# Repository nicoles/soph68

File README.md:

# soph68

Hey look, another 65%! 
This one has no underglow or hotswap, uses the magicforce layout. Very compatible layout for keycap sets, takes pcb mount stabs, supports single color led backlight.

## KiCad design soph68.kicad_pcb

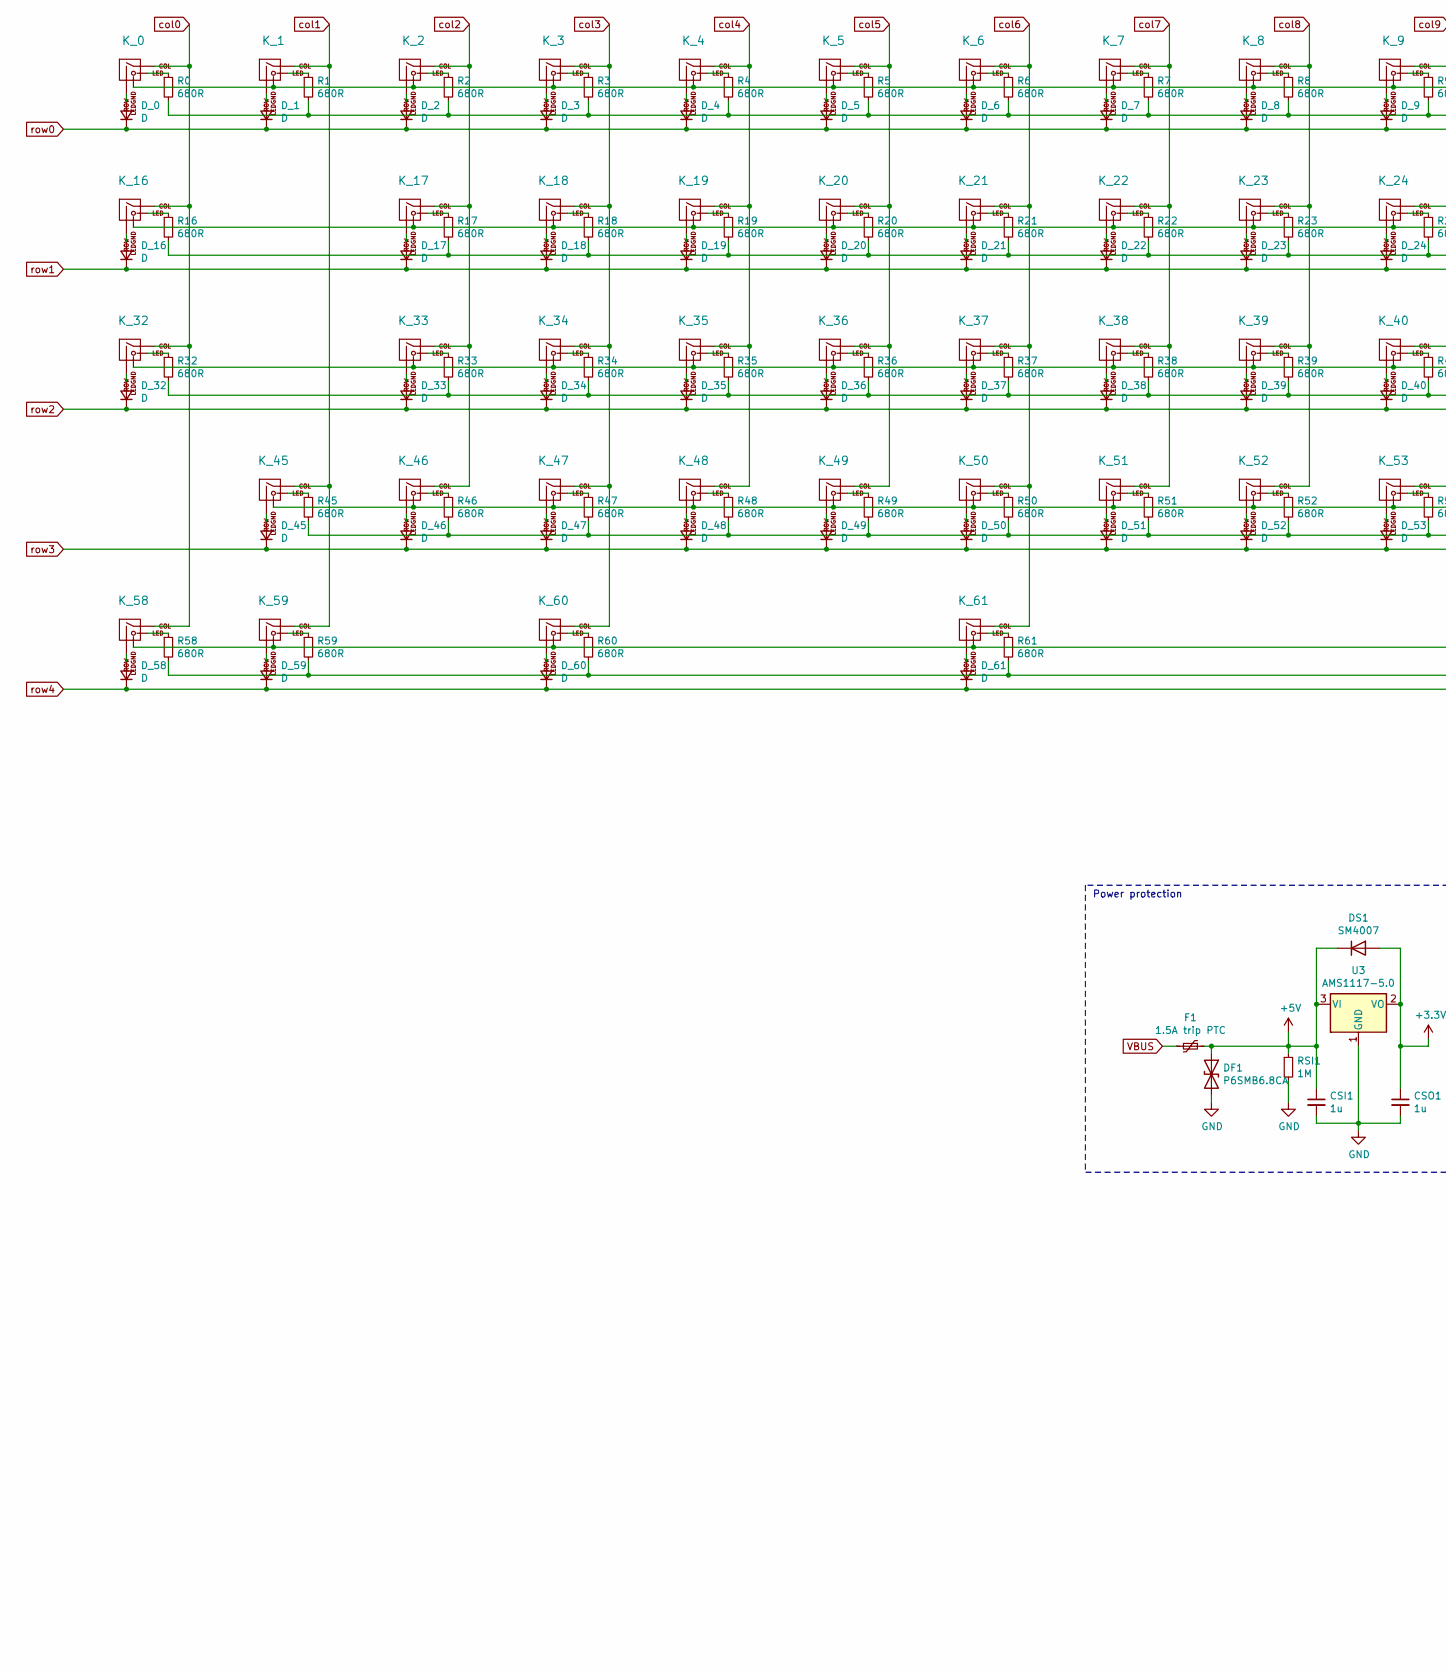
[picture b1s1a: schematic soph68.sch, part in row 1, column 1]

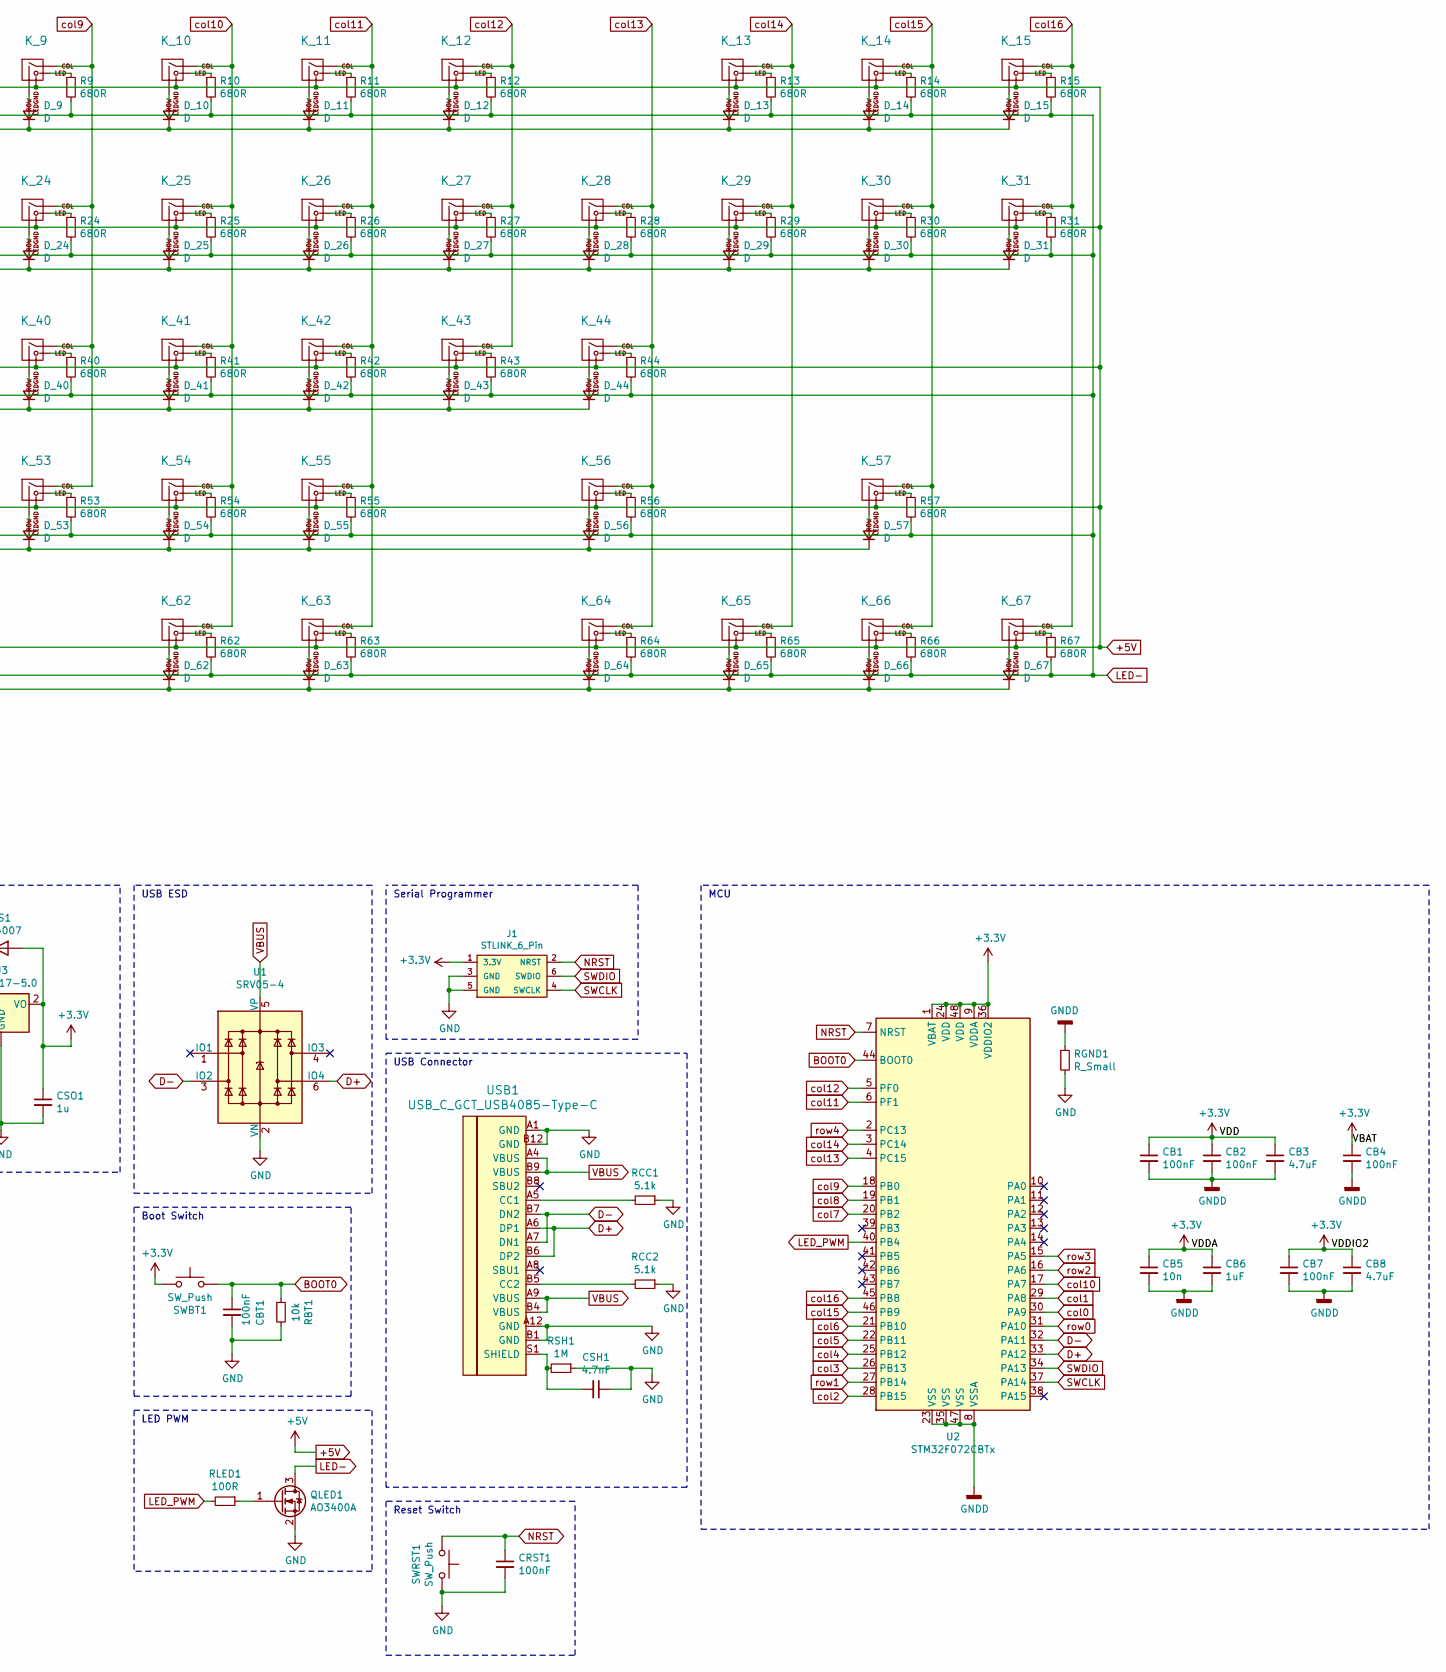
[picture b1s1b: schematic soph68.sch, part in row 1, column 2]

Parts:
CB1, CB2, CB4, CB7: 100nF; C_0402_1005Metric; JLCCode C1525
CB3, CB8: 4.7uF; C_0402_1005Metric; JLCCode C23733
CB5: 10n; C_0402_1005Metric; JLCCode C15195
CB6: 1uF; C_0402_1005Metric; JLCCode C52923
CBT1: 100nF; C_0402_1005Metric; JLCCode C1525
CRST1: 100nF; C_0402_1005Metric; JLCCode C1525
CSH1: 4.7nF; C_0805_2012Metric; JLCCode C1744
CSI1: 1u; C_0805_2012Metric; JLCCode C28323
CSO1: 1u; C_0805_2012Metric; JLCCode C28323
DF1: P6SMB6.8CA; D_SMB; JLCCode C78395
DS1: SM4007; D_MELF; JLCCode C64898
D_0, D_1, D_2, D_3, D_4, D_5, D_6, D_7, D_8, D_9, D_10, D_11, D_12, D_13, D_14, D_15, D_16, D_17, D_18, D_19, D_20, D_21, D_22, D_23, D_24, D_25, D_26, D_27, D_28, D_29, D_30, D_31, D_32, D_33, D_34, D_35, D_36, D_37, D_38, D_39, D_40, D_41, D_42, D_43, D_44, D_45, D_46, D_47, D_48, D_49, D_50, D_51, D_52, D_53, D_54, D_55, D_56, D_57, D_58, D_59, D_60, D_61, D_62, D_63, D_64, D_65, D_66, D_67: D; D_SOD-323F; JLCCode C81598
F1: 1.5A trip PTC; Fuse_1812_4532Metric; JLCCode C84140
J1: STLINK_6_Pin; 2X3_LOCK
K_0, K_1, K_2, K_3, K_4, K_5, K_6, K_7, K_8, K_9, K_10, K_11, K_12, K_14, K_15, K_17, K_18, K_19, K_20, K_21, K_22, K_23, K_24, K_25, K_26, K_27, K_28, K_30, K_31, K_33, K_34, K_35, K_36, K_37, K_38, K_39, K_40, K_41, K_42, K_43, K_46, K_47, K_48, K_49, K_50, K_51, K_52, K_53, K_54, K_55, K_57, K_65, K_66, K_67: KEYSW; MXOnly-1U
K_13: KEYSW; MXOnly-2U
K_16, K_29: KEYSW; MXOnly-1.5U
K_32: KEYSW; MXOnly-1.75U
K_44, K_45: KEYSW; MXOnly-2.25U
K_56: KEYSW; MXOnly-2.75U
K_58, K_59, K_60, K_62, K_63, K_64: KEYSW; MXOnly-1.25U
K_61: KEYSW; MXOnly-6.25U
QLED1: AO3400A; SOT-23; JLCCode C20917
R0, R1, R2, R3, R4, R5, R6, R7, R8, R9, R10, R11, R12, R13, R14, R15, R16, R17, R18, R19, R20, R21, R22, R23, R24, R25, R26, R27, R28, R29, R30, R31, R32, R33, R34, R35, R36, R37, R38, R39, R40, R41, R42, R43, R44, R45, R46, R47, R48, R49, R50, R51, R52, R53, R54, R55, R56, R57, R58, R59, R60, R61, R62, R63, R64, R65, R66, R67: 680R; R_0603_1608Metric; JLCCode C23228
RBT1: 10k; R_0805_2012Metric; JLCCode C17414
RCC1, RCC2: 5.1k; R_0805_2012Metric; JLCCode C27834
RGND1: R_Small; R_1206_3216Metric; JLCCode C127703
RLED1: 100R; R_0402_1005Metric; JLCCode C25076
RSH1: 1M; R_0805_2012Metric; JLCCode C17514
RSI1: 1M; C_0805_2012Metric; JLCCode C17514
SWBT1: SW_Push; SW_SPST_SKQG_WithStem; JLCCode C318884
SWRST1: SW_Push; SW_SPST_SKQG_WithStem; JLCCode C318884
U1: SRV05-4; SOT-23-6; JLCCode C85364
U2: STM32F072CBTx; LQFP-48_7x7mm_P0.5mm; JLCCode C81720
U3: AMS1117-5.0; SOT-223-3_TabPin2; JLCCode C6187
USB1: USB_C_GCT_USB4085-Type-C; USB_C_Receptacle_GCT_USB4085

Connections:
+3V3: CB1.1, CB2.1, CB3.1, CB4.1, CB5.1, CB6.1, CB7.1, CB8.1, CSO1.1, DS1.2 (A), J1.1 (3.3V), SWBT1.1, U2.1 (VBAT), U2.9 (VDDA), U2.24 (VDD), U2.36 (VDDIO2), U2.48 (VDD), U3.2 (VO)
+5V: CSI1.1, DF1.1 (A1), DS1.1 (K), F1.1, K_0.4 (LEDGND), K_1.4 (LEDGND), K_2.4 (LEDGND), K_3.4 (LEDGND), K_4.4 (LEDGND), K_5.4 (LEDGND), K_6.4 (LEDGND), K_7.4 (LEDGND), K_8.4 (LEDGND), K_9.4 (LEDGND), K_10.4 (LEDGND), K_11.4 (LEDGND), K_12.4 (LEDGND), K_13.4 (LEDGND), K_14.4 (LEDGND), K_15.4 (LEDGND), K_16.4 (LEDGND), K_17.4 (LEDGND), K_18.4 (LEDGND), K_19.4 (LEDGND), K_20.4 (LEDGND), K_21.4 (LEDGND), K_22.4 (LEDGND), K_23.4 (LEDGND), K_24.4 (LEDGND), K_25.4 (LEDGND), K_26.4 (LEDGND), K_27.4 (LEDGND), K_28.4 (LEDGND), K_29.4 (LEDGND), K_30.4 (LEDGND), K_31.4 (LEDGND), K_32.4 (LEDGND), K_33.4 (LEDGND), K_34.4 (LEDGND), K_35.4 (LEDGND), K_36.4 (LEDGND), K_37.4 (LEDGND), K_38.4 (LEDGND), K_39.4 (LEDGND), K_40.4 (LEDGND), K_41.4 (LEDGND), K_42.4 (LEDGND), K_43.4 (LEDGND), K_44.4 (LEDGND), K_45.4 (LEDGND), K_46.4 (LEDGND), K_47.4 (LEDGND), K_48.4 (LEDGND), K_49.4 (LEDGND), K_50.4 (LEDGND), K_51.4 (LEDGND), K_52.4 (LEDGND), K_53.4 (LEDGND), K_54.4 (LEDGND), K_55.4 (LEDGND), K_56.4 (LEDGND), K_57.4 (LEDGND), K_58.4 (LEDGND), K_59.4 (LEDGND), K_60.4 (LEDGND), K_61.4 (LEDGND), K_62.4 (LEDGND), K_63.4 (LEDGND), K_64.4 (LEDGND), K_65.4 (LEDGND), K_66.4 (LEDGND), K_67.4 (LEDGND), RSI1.1, U3.3 (VI)
BOOT0: CBT1.1, RBT1.1, SWBT1.2, U2.44 (BOOT0)
D+: U1.6 (IO4), U2.33 (PA12), USB1.A6 (DP1), USB1.B6 (DP2)
D-: U1.3 (IO2), U2.32 (PA11), USB1.A7 (DN1), USB1.B7 (DN2)
GND: CBT1.2, CRST1.2, CSH1.1, CSI1.2, CSO1.2, DF1.2 (A2), J1.3 (GND), J1.5 (GND), QLED1.2 (S), RBT1.2, RCC1.1, RCC2.1, RGND1.2, RSH1.1, RSI1.2, SWRST1.2, U1.2 (VN), U3.1 (GND), USB1.A1 (GND), USB1.A12 (GND), USB1.B1 (GND), USB1.B12 (GND)
GNDD: CB1.2, CB2.2, CB3.2, CB4.2, CB5.2, CB6.2, CB7.2, CB8.2, RGND1.1, U2.8 (VSSA), U2.23 (VSS), U2.35 (VSS), U2.47 (VSS)
LED-: QLED1.3 (D), R0.2, R1.2, R2.2, R3.2, R4.2, R5.2, R6.2, R7.2, R8.2, R9.2, R10.2, R11.2, R12.2, R13.2, R14.2, R15.2, R16.2, R17.2, R18.2, R19.2, R20.2, R21.2, R22.2, R23.2, R24.2, R25.2, R26.2, R27.2, R28.2, R29.2, R30.2, R31.2, R32.2, R33.2, R34.2, R35.2, R36.2, R37.2, R38.2, R39.2, R40.2, R41.2, R42.2, R43.2, R44.2, R45.2, R46.2, R47.2, R48.2, R49.2, R50.2, R51.2, R52.2, R53.2, R54.2, R55.2, R56.2, R57.2, R58.2, R59.2, R60.2, R61.2, R62.2, R63.2, R64.2, R65.2, R66.2, R67.2
LED_PWM: RLED1.2, U2.40 (PB4)
NRST: CRST1.1, J1.2 (NRST), SWRST1.1, U2.7 (NRST)
unnamed: CSH1.2, RSH1.2, USB1.S1 (SHIELD)
unnamed: D_0.2 (A), K_0.2 (ROW)
unnamed: D_1.2 (A), K_1.2 (ROW)
unnamed: D_2.2 (A), K_2.2 (ROW)
unnamed: D_3.2 (A), K_3.2 (ROW)
unnamed: D_4.2 (A), K_4.2 (ROW)
unnamed: D_5.2 (A), K_5.2 (ROW)
unnamed: D_6.2 (A), K_6.2 (ROW)
unnamed: D_7.2 (A), K_7.2 (ROW)
unnamed: D_8.2 (A), K_8.2 (ROW)
unnamed: D_9.2 (A), K_9.2 (ROW)
unnamed: D_10.2 (A), K_10.2 (ROW)
unnamed: D_11.2 (A), K_11.2 (ROW)
unnamed: D_12.2 (A), K_12.2 (ROW)
unnamed: D_13.2 (A), K_13.2 (ROW)
unnamed: D_14.2 (A), K_14.2 (ROW)
unnamed: D_15.2 (A), K_15.2 (ROW)
unnamed: D_16.2 (A), K_16.2 (ROW)
unnamed: D_17.2 (A), K_17.2 (ROW)
unnamed: D_18.2 (A), K_18.2 (ROW)
unnamed: D_19.2 (A), K_19.2 (ROW)
unnamed: D_20.2 (A), K_20.2 (ROW)
unnamed: D_21.2 (A), K_21.2 (ROW)
unnamed: D_22.2 (A), K_22.2 (ROW)
unnamed: D_23.2 (A), K_23.2 (ROW)
unnamed: D_24.2 (A), K_24.2 (ROW)
unnamed: D_25.2 (A), K_25.2 (ROW)
unnamed: D_26.2 (A), K_26.2 (ROW)
unnamed: D_27.2 (A), K_27.2 (ROW)
unnamed: D_28.2 (A), K_28.2 (ROW)
unnamed: D_29.2 (A), K_29.2 (ROW)
unnamed: D_30.2 (A), K_30.2 (ROW)
unnamed: D_31.2 (A), K_31.2 (ROW)
unnamed: D_32.2 (A), K_32.2 (ROW)
unnamed: D_33.2 (A), K_33.2 (ROW)
unnamed: D_34.2 (A), K_34.2 (ROW)
unnamed: D_35.2 (A), K_35.2 (ROW)
unnamed: D_36.2 (A), K_36.2 (ROW)
unnamed: D_37.2 (A), K_37.2 (ROW)
unnamed: D_38.2 (A), K_38.2 (ROW)
unnamed: D_39.2 (A), K_39.2 (ROW)
unnamed: D_40.2 (A), K_40.2 (ROW)
unnamed: D_41.2 (A), K_41.2 (ROW)
unnamed: D_42.2 (A), K_42.2 (ROW)
unnamed: D_43.2 (A), K_43.2 (ROW)
unnamed: D_44.2 (A), K_44.2 (ROW)
unnamed: D_45.2 (A), K_45.2 (ROW)
unnamed: D_46.2 (A), K_46.2 (ROW)
unnamed: D_47.2 (A), K_47.2 (ROW)
unnamed: D_48.2 (A), K_48.2 (ROW)
unnamed: D_49.2 (A), K_49.2 (ROW)
unnamed: D_50.2 (A), K_50.2 (ROW)
unnamed: D_51.2 (A), K_51.2 (ROW)
unnamed: D_52.2 (A), K_52.2 (ROW)
unnamed: D_53.2 (A), K_53.2 (ROW)
unnamed: D_54.2 (A), K_54.2 (ROW)
unnamed: D_55.2 (A), K_55.2 (ROW)
unnamed: D_56.2 (A), K_56.2 (ROW)
unnamed: D_57.2 (A), K_57.2 (ROW)
unnamed: D_58.2 (A), K_58.2 (ROW)
unnamed: D_59.2 (A), K_59.2 (ROW)
unnamed: D_60.2 (A), K_60.2 (ROW)
unnamed: D_61.2 (A), K_61.2 (ROW)
unnamed: D_62.2 (A), K_62.2 (ROW)
unnamed: D_63.2 (A), K_63.2 (ROW)
unnamed: D_64.2 (A), K_64.2 (ROW)
unnamed: D_65.2 (A), K_65.2 (ROW)
unnamed: D_66.2 (A), K_66.2 (ROW)
unnamed: D_67.2 (A), K_67.2 (ROW)
unnamed: K_0.3 (LED), R0.1
unnamed: K_1.3 (LED), R1.1
unnamed: K_2.3 (LED), R2.1
unnamed: K_3.3 (LED), R3.1
unnamed: K_4.3 (LED), R4.1
unnamed: K_5.3 (LED), R5.1
unnamed: K_6.3 (LED), R6.1
unnamed: K_7.3 (LED), R7.1
unnamed: K_8.3 (LED), R8.1
unnamed: K_9.3 (LED), R9.1
unnamed: K_10.3 (LED), R10.1
unnamed: K_11.3 (LED), R11.1
unnamed: K_12.3 (LED), R12.1
unnamed: K_13.3 (LED), R13.1
unnamed: K_14.3 (LED), R14.1
unnamed: K_15.3 (LED), R15.1
unnamed: K_16.3 (LED), R16.1
unnamed: K_17.3 (LED), R17.1
unnamed: K_18.3 (LED), R18.1
unnamed: K_19.3 (LED), R19.1
unnamed: K_20.3 (LED), R20.1
unnamed: K_21.3 (LED), R21.1
unnamed: K_22.3 (LED), R22.1
unnamed: K_23.3 (LED), R23.1
unnamed: K_24.3 (LED), R24.1
unnamed: K_25.3 (LED), R25.1
unnamed: K_26.3 (LED), R26.1
unnamed: K_27.3 (LED), R27.1
unnamed: K_28.3 (LED), R28.1
unnamed: K_29.3 (LED), R29.1
unnamed: K_30.3 (LED), R30.1
unnamed: K_31.3 (LED), R31.1
unnamed: K_32.3 (LED), R32.1
unnamed: K_33.3 (LED), R33.1
unnamed: K_34.3 (LED), R34.1
unnamed: K_35.3 (LED), R35.1
unnamed: K_36.3 (LED), R36.1
unnamed: K_37.3 (LED), R37.1
unnamed: K_38.3 (LED), R38.1
unnamed: K_39.3 (LED), R39.1
unnamed: K_40.3 (LED), R40.1
unnamed: K_41.3 (LED), R41.1
unnamed: K_42.3 (LED), R42.1
unnamed: K_43.3 (LED), R43.1
unnamed: K_44.3 (LED), R44.1
unnamed: K_45.3 (LED), R45.1
unnamed: K_46.3 (LED), R46.1
unnamed: K_47.3 (LED), R47.1
unnamed: K_48.3 (LED), R48.1
unnamed: K_49.3 (LED), R49.1
unnamed: K_50.3 (LED), R50.1
unnamed: K_51.3 (LED), R51.1
unnamed: K_52.3 (LED), R52.1
unnamed: K_53.3 (LED), R53.1
unnamed: K_54.3 (LED), R54.1
unnamed: K_55.3 (LED), R55.1
unnamed: K_56.3 (LED), R56.1
unnamed: K_57.3 (LED), R57.1
unnamed: K_58.3 (LED), R58.1
unnamed: K_59.3 (LED), R59.1
unnamed: K_60.3 (LED), R60.1
unnamed: K_61.3 (LED), R61.1
unnamed: K_62.3 (LED), R62.1
unnamed: K_63.3 (LED), R63.1
unnamed: K_64.3 (LED), R64.1
unnamed: K_65.3 (LED), R65.1
unnamed: K_66.3 (LED), R66.1
unnamed: K_67.3 (LED), R67.1
unnamed: QLED1.1 (G), RLED1.1
unnamed: RCC1.2, USB1.A5 (CC1)
unnamed: RCC2.2, USB1.B5 (CC2)
SWCLK: J1.4 (SWCLK), U2.37 (PA14)
SWDIO: J1.6 (SWDIO), U2.34 (PA13)
VBUS: F1.2, U1.5 (VP), USB1.A4 (VBUS), USB1.A9 (VBUS), USB1.B4 (VBUS), USB1.B9 (VBUS)
col0: K_0.1 (COL), K_16.1 (COL), K_32.1 (COL), K_58.1 (COL), U2.30 (PA9)
col1: K_1.1 (COL), K_45.1 (COL), K_59.1 (COL), U2.29 (PA8)
col2: K_2.1 (COL), K_17.1 (COL), K_33.1 (COL), K_46.1 (COL), U2.28 (PB15)
col3: K_3.1 (COL), K_18.1 (COL), K_34.1 (COL), K_47.1 (COL), K_60.1 (COL), U2.26 (PB13)
col4: K_4.1 (COL), K_19.1 (COL), K_35.1 (COL), K_48.1 (COL), U2.25 (PB12)
col5: K_5.1 (COL), K_20.1 (COL), K_36.1 (COL), K_49.1 (COL), U2.22 (PB11)
col6: K_6.1 (COL), K_21.1 (COL), K_37.1 (COL), K_50.1 (COL), K_61.1 (COL), U2.21 (PB10)
col7: K_7.1 (COL), K_22.1 (COL), K_38.1 (COL), K_51.1 (COL), U2.20 (PB2)
col8: K_8.1 (COL), K_23.1 (COL), K_39.1 (COL), K_52.1 (COL), U2.19 (PB1)
col9: K_9.1 (COL), K_24.1 (COL), K_40.1 (COL), K_53.1 (COL), U2.18 (PB0)
col10: K_10.1 (COL), K_25.1 (COL), K_41.1 (COL), K_54.1 (COL), K_62.1 (COL), U2.17 (PA7)
col11: K_11.1 (COL), K_26.1 (COL), K_42.1 (COL), K_55.1 (COL), K_63.1 (COL), U2.6 (PF1)
col12: K_12.1 (COL), K_27.1 (COL), K_43.1 (COL), U2.5 (PF0)
col13: K_28.1 (COL), K_44.1 (COL), K_56.1 (COL), K_64.1 (COL), U2.4 (PC15)
col14: K_13.1 (COL), K_29.1 (COL), K_65.1 (COL), U2.3 (PC14)
col15: K_14.1 (COL), K_30.1 (COL), K_57.1 (COL), K_66.1 (COL), U2.46 (PB9)
col16: K_15.1 (COL), K_31.1 (COL), K_67.1 (COL), U2.45 (PB8)
row0: D_0.1 (K), D_1.1 (K), D_2.1 (K), D_3.1 (K), D_4.1 (K), D_5.1 (K), D_6.1 (K), D_7.1 (K), D_8.1 (K), D_9.1 (K), D_10.1 (K), D_11.1 (K), D_12.1 (K), D_13.1 (K), D_14.1 (K), D_15.1 (K), U2.31 (PA10)
row1: D_16.1 (K), D_17.1 (K), D_18.1 (K), D_19.1 (K), D_20.1 (K), D_21.1 (K), D_22.1 (K), D_23.1 (K), D_24.1 (K), D_25.1 (K), D_26.1 (K), D_27.1 (K), D_28.1 (K), D_29.1 (K), D_30.1 (K), D_31.1 (K), U2.27 (PB14)
row2: D_32.1 (K), D_33.1 (K), D_34.1 (K), D_35.1 (K), D_36.1 (K), D_37.1 (K), D_38.1 (K), D_39.1 (K), D_40.1 (K), D_41.1 (K), D_42.1 (K), D_43.1 (K), D_44.1 (K), U2.16 (PA6)
row3: D_45.1 (K), D_46.1 (K), D_47.1 (K), D_48.1 (K), D_49.1 (K), D_50.1 (K), D_51.1 (K), D_52.1 (K), D_53.1 (K), D_54.1 (K), D_55.1 (K), D_56.1 (K), D_57.1 (K), U2.15 (PA5)
row4: D_58.1 (K), D_59.1 (K), D_60.1 (K), D_61.1 (K), D_62.1 (K), D_63.1 (K), D_64.1 (K), D_65.1 (K), D_66.1 (K), D_67.1 (K), U2.2 (PC13)

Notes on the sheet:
Serial Programmer
USB ESD
USB Connector
MCU
Reset Switch
LED PWM
Boot Switch
Power protection

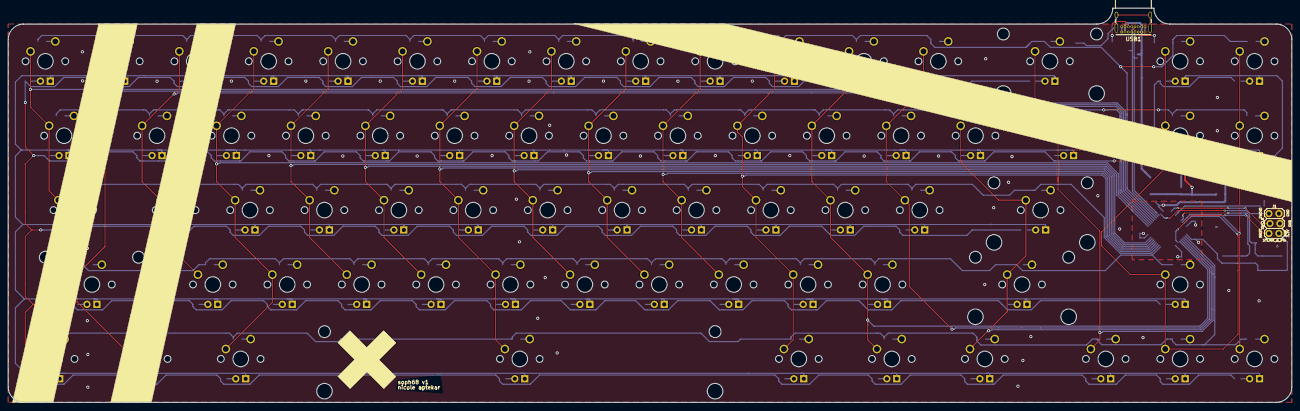
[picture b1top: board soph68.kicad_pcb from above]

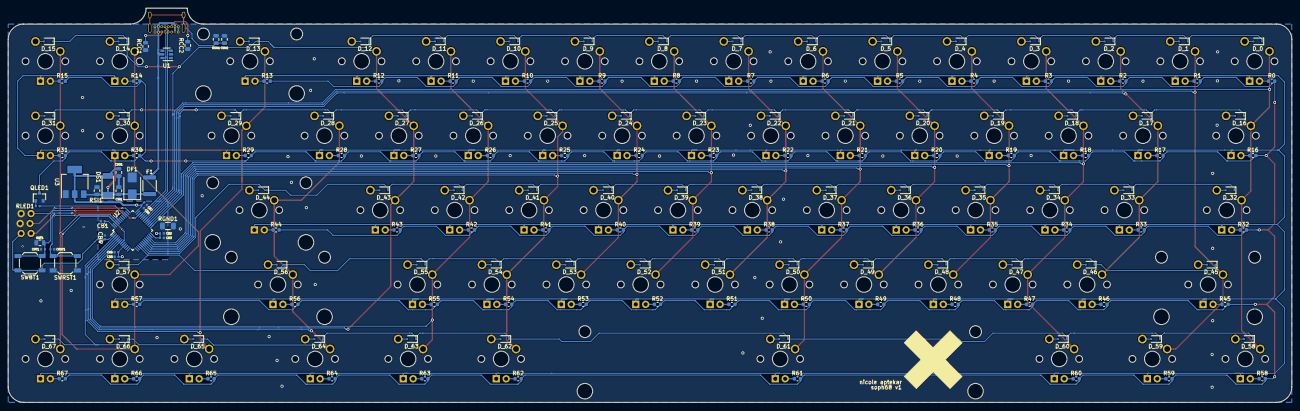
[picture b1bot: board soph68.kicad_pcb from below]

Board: 2 copper layers, 328.6 x 100.9 mm, 235 parts (165 on the bottom side), 175 nets.

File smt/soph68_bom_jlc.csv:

"Comment","Designator","Footprint","LCSC Part #"
"100nF","CB1,CB2,CB7,CB4","C_0402_1005Metric","C1525"
"4.7uF","CB3,CB8","C_0402_1005Metric","C23733"
"10n","CB5","C_0402_1005Metric","C15195"
"1uF","CB6","C_0402_1005Metric","C52923"
"100nF","CBT1","C_0402_1005Metric","C1525"
"100nF","CRST1","C_0402_1005Metric","C1525"
"4.7nF","CSH1","C_0805_2012Metric","C1744"
"1u","CSI1","C_0805_2012Metric","C28323"
"1u","CSO1","C_0805_2012Metric","C28323"
"D","D_0,D_1,D_2,D_3,D_4,D_5,D_6,D_7,D_8,D_9,D_10,D_11,D_12,D_13,D_14,D_16,D_17,D_18,D_19,D_20,D_21,D_22,D_23,D_24,D_25,D_26,D_27,D_28,D_29,D_30,D_31,D_32,D_33,D_34,D_35,D_36,D_37,D_38,D_39,D_40,D_41,D_42,D_43,D_44,D_45,D_46,D_47,D_48,D_49,D_50,D_51,D_52,D_53,D_54,D_55,D_56,D_57,D_58,D_59,D_60,D_61,D_62,D_63,D_64,D_65,D_66,D_67,D_15","D_SOD-323F","C81598"
"P6SMB6.8CA","DF1","D_SMB","C78395"
"SM4007","DS1","D_MELF","C64898"
"1.5A trip PTC","F1","Fuse_1812_4532Metric","C84140"
"AO3400A","QLED1","SOT-23","C20917"
"680R","R0,R1,R2,R3,R4,R5,R6,R7,R8,R9,R10,R11,R12,R13,R14,R15,R31,R30,R29,R28,R27,R26,R25,R24,R23,R22,R21,R20,R19,R18,R17,R16,R32,R33,R34,R35,R36,R37,R38,R39,R40,R41,R42,R43,R44,R45,R46,R47,R48,R49,R50,R51,R52,R53,R54,R55,R56,R57,R67,R66,R65,R64,R63,R62,R61,R60,R59,R58","R_0603_1608Metric","C23228"
"10k","RBT1","R_0805_2012Metric","C17414"
"5.1k","RCC2,RCC1","R_0805_2012Metric","C27834"
"R_Small","RGND1","R_1206_3216Metric","C127703"
"100R","RLED1","R_0402_1005Metric","C25076"
"1M","RSH1","R_0805_2012Metric","C17514"
"1M","RSI1","C_0805_2012Metric","C17514"
"SW_Push","SWBT1","SW_SPST_SKQG_WithStem","C318884"
"SW_Push","SWRST1","SW_SPST_SKQG_WithStem","C318884"
"SRV05-4","U1","SOT-23-6","C85364"
"STM32F072CBTx","U2","LQFP-48_7x7mm_P0.5mm","C81720"
"AMS1117-5.0","U3","SOT-223-3_TabPin2","C6187"

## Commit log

2020-07-02 Complete board without mounting holes or decoration
    Also first commit, because i am responsible for git crimes
2020-07-02 Added logo
2020-07-02 fixing some schema troubles
2020-07-02 Added a box to the power protection biz in the schema
2020-07-03 Rerouted things to get rid of 45s
2020-07-03 Changed vias a bit
2020-07-03 added jlccode for diodes
2020-07-03 added fancy stripes
2020-07-03 Changed to cbtx
2020-07-03 added gerbers and smt assembly files
